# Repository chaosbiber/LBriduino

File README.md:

# LBriduino
## Description
This is a PCB design for keencave's [LBridge](https://github.com/keencave/LBridge) code. It's my very first design and still in testing, dragons beware!

Made with free version of EAGLE for BM019 and RFDuino.

The switch has the states On (1-2) and Off/Testing (2-3). The battery can be charged in any state, in the off-state power for the NFC and RFDuino modules is disconnected. But there are two testing vias that can be shorted or connected to an ampere meter.

## Parts
(product links from 2017/12/10)

* BM019  
http://www.solutions-cubed.com/bm019/  
http://www.warburtech.co.uk/products/modules/solutions.cubed.bm019.serial.to.nfc.converter/
* RFduino RFD22301  
https://www.mouser.de/ProductDetail/RF-Digital-Wireless/RFD22301/
* Lipo Charger IC MCP73831T-2ACI/OT
* C1/C2: Capacitor 0603 4.7µF (measured 3.8µF)
* C3: Capacitor 0603 100nF (to program RFDuino, smaller capacity was recommended but 100nF works for me)
* R1: 330 Ohm
* R2: 3kOhm (for ~333mA charging speed, default 2kOhm for ~500mA. Ic = 1000/R2)
* red LED 0603
* Sliding switch SPDT (generic, I ordered Apem MHSS1105)
* Molex 105017-0001 USB micro-B connector
* USB programmer for the RFDuino (RFD22121), or any adapter with serial connection at 3.3V level

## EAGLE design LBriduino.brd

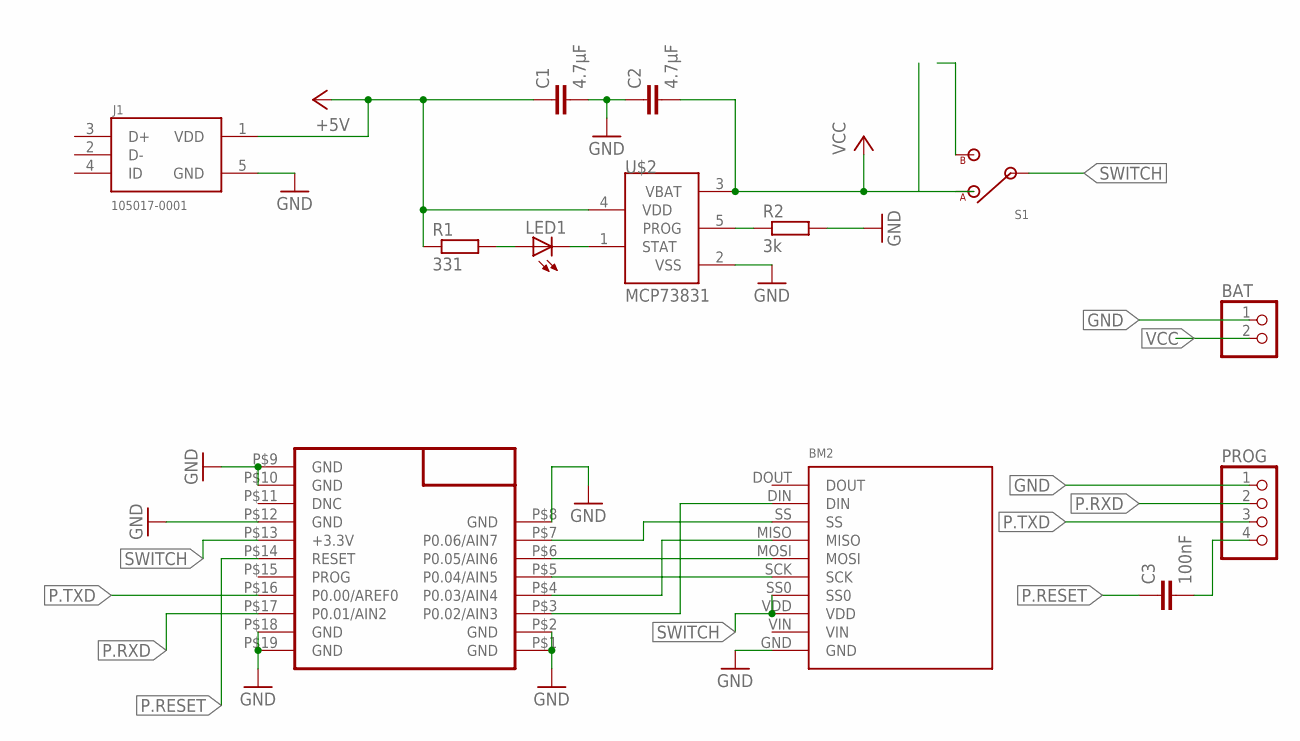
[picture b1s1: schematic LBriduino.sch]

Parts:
BAT: PINHD-1X2; 1X02
BM2: BM019
C1, C2: 4.7µF; C0603
C3: 100nF; C0603
J1: 105017-0001; MOLEX_105017-0001
LED1: LEDCHIP-LED0603; CHIP-LED0603
PROG: PINHD-1X4; 1X04
R1: 331; R0603
R2: 3k; R0603
S1: STS121PC04
U$1: RFD22301; RFD21733
U$2: MCP73831; SOT23-5L

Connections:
+5V: C1.1, J1.1 (VDD), R1.1, U$2.4 (VDD)
GND: BAT.1, BM2.GND, C1.2, C2.1, J1.5 (GND), PROG.1, R2.2, U$1.P$1 (GND), U$1.P$2 (GND), U$1.P$8 (GND), U$1.P$9 (GND), U$1.P$10 (GND), U$1.P$12 (GND), U$1.P$18 (GND), U$1.P$19 (GND), U$2.2 (VSS)
IRQ: BM2.DIN, U$1.P$3 (P0.02/AIN3)
MISO: BM2.MISO, U$1.P$4 (P0.03/AIN4)
MOSI: BM2.MOSI, U$1.P$6 (P0.05/AIN6)
unnamed: LED1.A, R1.2
unnamed: LED1.C, U$2.1 (STAT)
unnamed: C3.2, PROG.4
unnamed: R2.1, U$2.5 (PROG)
P.RESET: C3.1, U$1.P$14 (RESET)
P.RXD: PROG.2, U$1.P$17 (P0.01/AIN2)
P.TXD: PROG.3, U$1.P$16 (P0.00/AREF0)
SCK: BM2.SCK, U$1.P$5 (P0.04/AIN5)
SS: BM2.SS, U$1.P$7 (P0.06/AIN7)
SWITCH: BM2.SS0, BM2.VDD, S1.2, U$1.P$13 (+3.3V)
TEST: S1.3
VCC: BAT.2, C2.2, S1.1, U$2.3 (VBAT)

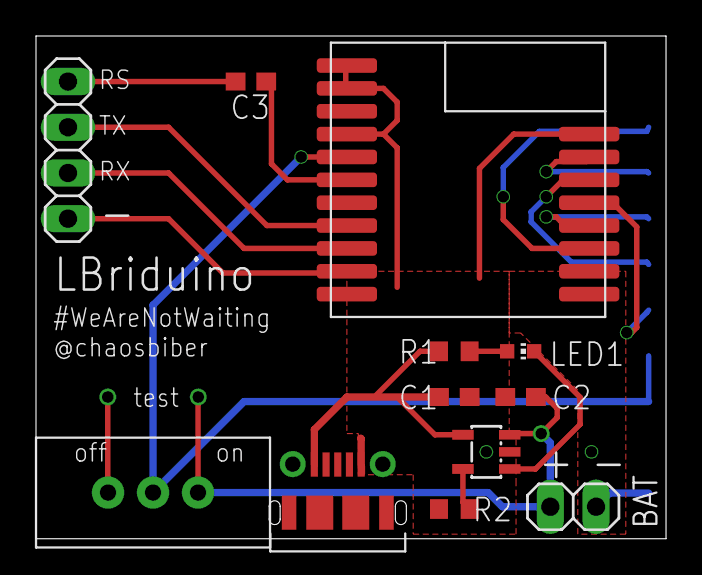
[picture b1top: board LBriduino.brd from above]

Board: 2 copper layers, 35.0 x 27.9 mm, 13 parts (1 on the bottom side), 16 nets.

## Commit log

2017-12-11 added board files, README and screenshot
2017-12-11 fix headers in README.md
2017-12-11 minor re-wireing, updated pic, specified usb connector in description
2017-12-11 reduced groundplane, used traces instead
2017-12-11 changed BM019 voltage input from VIN to VDD, added testing points for ampere meter in off-mode
2017-12-11 reverted BM019 input to VIN
2017-12-11 added C3 and testing points to README.md
2018-01-02 bug report
2018-01-11 redesign: missing ground bugfix, charging-IC-cooling, bluetooth-area copper-free
2018-01-12 made it smaller
